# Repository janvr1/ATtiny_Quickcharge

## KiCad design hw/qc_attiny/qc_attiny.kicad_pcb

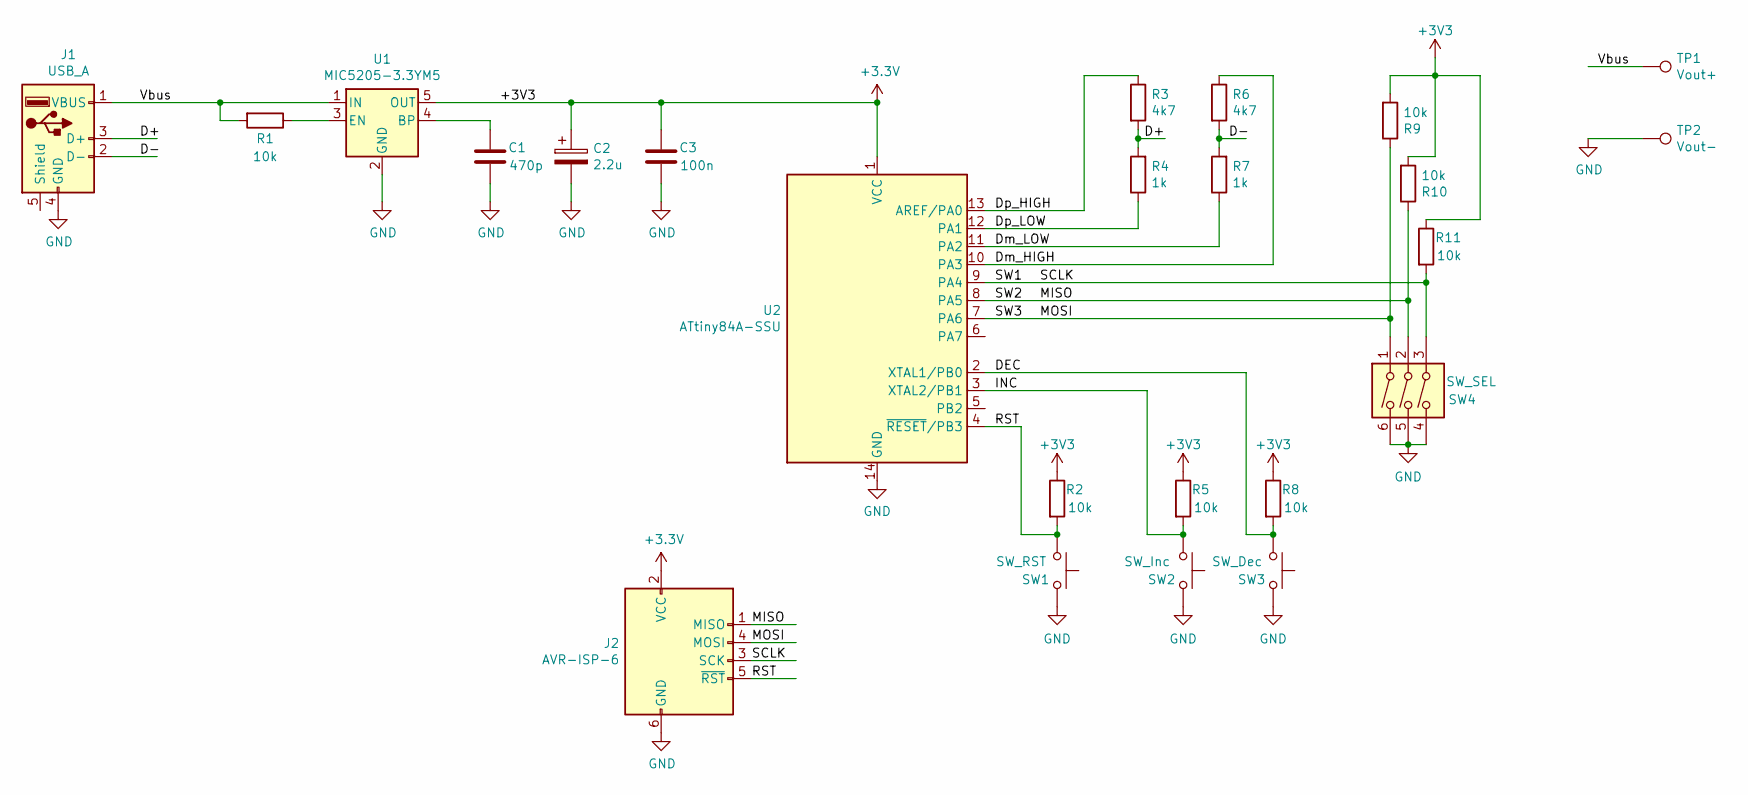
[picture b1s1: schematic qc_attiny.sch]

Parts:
C1: 470p; C_1206_3216Metric_Pad1.33x1.80mm_HandSolder
C2: 2.2u; CP_EIA-3216-18_Kemet-A_Pad1.58x1.35mm_HandSolder
C3: 100n; C_1206_3216Metric_Pad1.33x1.80mm_HandSolder
J1: USB_A; USB-A_Multicomp
J2: AVR-ISP-6; PinHeader_2x03_P2.54mm_Vertical
R1, R2, R5, R8, R9, R10, R11: 10k; R_1206_3216Metric_Pad1.30x1.75mm_HandSolder
R3, R6: 4k7; R_1206_3216Metric_Pad1.30x1.75mm_HandSolder
R4, R7: 1k; R_1206_3216Metric_Pad1.30x1.75mm_HandSolder
SW1: SW_RST; Push_Button_6x6mm
SW2: SW_Inc; Push_Button_6x6mm
SW3: SW_Dec; Push_Button_6x6mm
SW4: SW_SEL; SW_DIP_SPSTx03_Slide_9.78x9.8mm_W7.62mm_P2.54mm
TP1: Vout+; TestPoint_Pad_3.0x3.0mm
TP2: Vout-; TestPoint_Pad_3.0x3.0mm
U1: MIC5205-3.3YM5; SOT-23-5
U2: ATtiny84A-SSU; SOIC-14_3.9x8.7mm_P1.27mm

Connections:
+3V3: C2.1, C3.2, J2.2 (VCC), R2.1, R5.1, R8.1, R9.2, R10.2, R11.1, U1.5 (OUT), U2.1 (VCC)
/D+: J1.3 (D+), R3.2, R4.2
/D-: J1.2 (D-), R6.2, R7.2
/DEC: R8.2, SW3.2, U2.2 (XTAL1/PB0)
/Dm_HIGH: R6.1, U2.10 (PA3)
/Dm_LOW: R7.1, U2.11 (PA2)
/Dp_HIGH: R3.1, U2.13 (AREF/PA0)
/Dp_LOW: R4.1, U2.12 (PA1)
/INC: R5.2, SW2.2, U2.3 (XTAL2/PB1)
/MISO: J2.1 (MISO), R10.1, SW4.2, U2.8 (PA5)
/MOSI: J2.4 (MOSI), R9.1, SW4.1, U2.7 (PA6)
/RST: J2.5 (~RST), R2.2, SW1.2, U2.4 (~RESET~/PB3)
/SCLK: J2.3 (SCK), R11.2, SW4.3, U2.9 (PA4)
/Vbus: J1.1 (VBUS), R1.2, TP1.1, U1.1 (IN)
GND: C1.1, C2.2, C3.1, J1.4 (GND), J2.6 (GND), SW1.1, SW2.1, SW3.1, SW4.4, SW4.5, SW4.6, TP2.1, U1.2 (GND), U2.14 (GND)
unnamed: C1.2, U1.4 (BP)
unnamed: R1.1, U1.3 (EN)

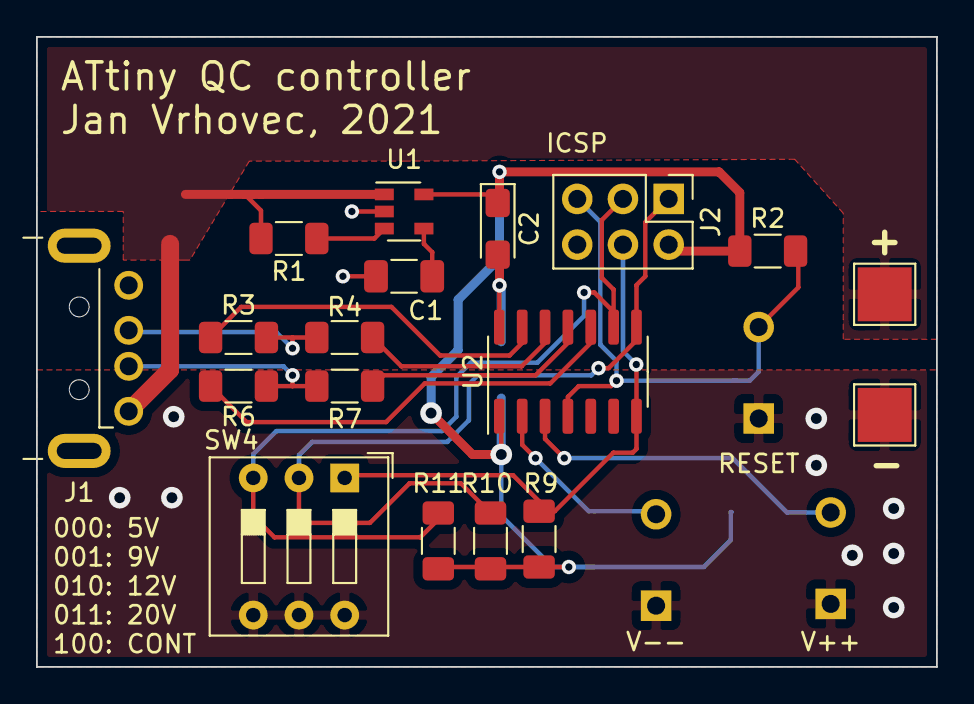
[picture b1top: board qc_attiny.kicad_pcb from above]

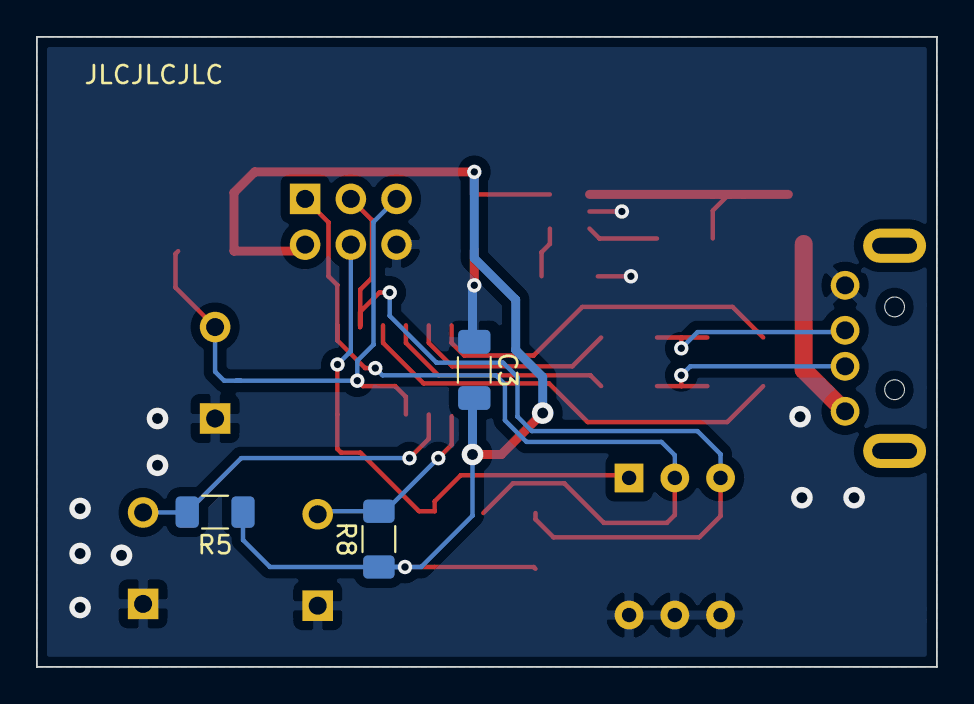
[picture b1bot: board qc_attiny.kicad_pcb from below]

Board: 2 copper layers, 50.0 x 35.0 mm, 24 parts (3 on the bottom side), 17 nets.

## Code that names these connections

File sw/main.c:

#include <avr/io.h>
#include <util/delay.h>

#define Dp_HIGH (1 << PORTA0) // Data+ high
#define Dp_LOW (1 << PORTA1)  // Data+ low
#define Dm_LOW (1 << PORTA2)  // Data- low
#define Dm_HIGH (1 << PORTA3) // Data- high

#define SW3 (1 << PORTA6)    // Dip switch position 3
#define SW2 (1 << PORTA5)    // Dip switch position 2
#define SW1 (1 << PORTA4)    // Dip switch position 1
#define SW_DEC (1 << PORTB1) // Decrement button
#define SW_INC (1 << PORTB0) // Increment button

#define READ_SW_INC ((PINB & SW_INC) >> PORTB0) // Macro to read button value
#define READ_SW_DEC ((PINB & SW_DEC) >> PORTB1) // -||-

typedef enum QC_VOLTAGE
{
    QC_5V = 0x07,
    QC_9V = 0x03,
    QC_12V = 0x05,
    QC_20V = 0x01,
    QC_CONT = 0x06
} qc_voltage_t;

void qc_init();
qc_voltage_t read_switch();
void qc_set_voltage(qc_voltage_t voltage);
void qc_increment(void);
void qc_decrement(void);

int main(void)
{

    MCUCR |= (1 << PUD);   // Disable all pullups
    DDRA |= 0b00001111;    // PORTA0..3 are outputs
    DDRA &= ~(0b01110000); // PORTA4..6 are inputs
    DDRB &= ~(0b00000011); // PORTB0..1 inputs

    qc_init();
    qc_voltage_t volt = read_switch();
    qc_set_voltage(volt);
    qc_voltage_t volt_new;

    while (1)
    {
        _delay_ms(50);
        volt_new = read_switch();
        if (volt_new != volt)
        {
            if (volt == QC_CONT)
            {
                qc_set_voltage(QC_5V);
                _delay_ms(50);
            }
            qc_set_voltage(volt_new);
            volt = volt_new;
        }
        if (volt == QC_CONT)
        {
            // Read increment switch
            if (READ_SW_INC == 0)
            {
                qc_increment();
                uint8_t cnt = 0;
                while (READ_SW_INC == 0)
                {
                    _delay_ms(5);
                    cnt++;
                    if (cnt > 50)
                    {
                        qc_increment();
                        cnt = 0;
                    }
                }
            }
            if (READ_SW_DEC == 0)
            {
                qc_decrement();
                uint8_t cnt = 0;
                while (READ_SW_INC == 0)
                {
                    _delay_ms(5);
                    cnt++;
                    if (cnt > 50)
                    {
                        qc_decrement();
                        cnt = 0;
                    }
                }
            }
        }
    }
    return 0;
}

void qc_init()
{
    // Apply a voltage between 0.325V and 2V to D+ for atleast 1.25 seconds
    // D+_high = HIGH & D+_low = LOW -> D+ = 0,6V
    PORTA &= ~(Dp_LOW | Dm_LOW);
    PORTA |= (Dp_HIGH | Dm_HIGH);
    _delay_ms(1500);
    // Discharge the D-voltage below 0.325V for at least 1ms while keep the D+ voltage above 0.325V
    // D-_high = LOW & D-_low = LOW -> D- = 0V
    PORTA &= ~(Dm_HIGH | Dm_LOW);
    _delay_ms(50); // Wait for D- to fully discharge
}

qc_voltage_t read_switch()
{
    // Read bits 4 and 5 of input, bitshift them right so they are first two bits of return value
    return (qc_voltage_t)((PINA & (SW1 | SW2 | SW3)) >> 4);
};

void qc_increment()
{
    qc_set_voltage(QC_20V);
    _delay_ms(50);
    qc_set_voltage(QC_CONT);
    _delay_ms(50);
}

void qc_decrement()
{
    qc_set_voltage(QC_12V);
    _delay_ms(50);
    qc_set_voltage(QC_CONT);
    _delay_ms(50);
}
void qc_set_voltage(qc_voltage_t voltage)
{
    switch (voltage)
    {
    case QC_5V:
        // D+ = 0,6V; D- = 0V
        PORTA |= Dp_HIGH;
        PORTA &= ~(Dp_LOW | Dm_HIGH | Dm_LOW);
        break;
    case QC_9V:
        // D+ = 3,3V; D- = 0,6V
        PORTA |= (Dp_HIGH | Dp_LOW | Dm_HIGH);
        PORTA &= ~Dm_LOW;
        break;
    case QC_12V:
        // D+ = 0,6V; D- = 0,6V
        PORTA |= (Dp_HIGH | Dm_HIGH);
        PORTA &= ~(Dp_LOW | Dm_LOW);
        break;
    case QC_20V:
        // D+ = 3,3V; D- = 3,3V
        PORTA |= (Dp_HIGH | Dp_LOW | Dm_HIGH | Dm_LOW);
        break;
    case QC_CONT:
        // D+ = 0,6V; D- = 3,3V
        PORTA |= (Dp_HIGH | Dm_LOW | Dm_HIGH);
        PORTA &= ~Dp_LOW;
        break;
    default:
        // D+ = 0,6V; D- = 0V
        PORTA |= Dp_HIGH;
        PORTA &= ~(Dp_LOW | Dm_HIGH | Dm_LOW);
        break;
        break;
    }
}

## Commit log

2020-10-28 First commit :)
2020-10-28 Added readme
2020-10-28 added gitignore
2020-10-29 Refactor
2020-10-30 Update shematic
2020-12-27 Added PCB
2021-01-23 Update PCB
2021-02-03 Bugfixed and improvements!
2021-02-04 Code improvements
